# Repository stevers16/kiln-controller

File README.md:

# Kiln Controller

A MicroPython-based lumber drying kiln controller for a passive solar kiln in the
Georgian Bay area of Ontario. Designed for drying hardwood lumber (maple and beech,
0.5--1 inch thick) using multi-stage schedules derived from USDA Forest Products
Laboratory references (FPL-GTR-57 and FPL-GTR-118).

The kiln is approximately 5 ft x 2 ft x 3 ft, heated passively by solar gain with a
500W ceramic PTC backup heater for shoulder-season use. A Raspberry Pi Pico 2W
controls all kiln hardware. Telemetry is transmitted over LoRa (~200m) to a Raspberry
Pi 4 at the cottage, which stores data in SQLite and serves a REST API for a Kivy
mobile app.

---

## Hardware

| Subsystem | Component |
|---|---|
| MCU | Raspberry Pi Pico 2W |
| Temperature / RH | 2x SHT31-D (I2C, 0x44 / 0x45) |
| Moisture probes | Resistive, voltage divider, AC excitation |
| Exhaust fan | Foxconn PVA080G12Q 80mm PWM, tach feedback |
| Circulation fans | 3x Thermalright TL-C12C 120mm PWM |
| Vent dampers | 2x MG90S servo (intake + exhaust) |
| Backup heater | 500W PTC + Fotek SSR-25DA + RY85 thermal fuse |
| Current monitoring | 2x INA219 (12V rail + 5V rail) |
| Display | JC035-HVGA-ST-02 3.5" UART serial, 320x480 |
| SD card | SPI micro SD (logging) |
| LoRa radio | AI-Thinker Ra-02 433 MHz (SX1278), TX-only |
| Remote server | Raspberry Pi 4 with Ra-02 receiver |

---

## Schematic and custom PCB

KiCad 9.0 project with schematic and custom PCB layout is in the PCB folder.

---

## Firmware (Pico 2W -- MicroPython)

All hardware drivers live in `lib/`. Every module is class-based, accepts pin numbers
as constructor arguments, and follows the pattern established in `lib/exhaust.py`.

| Module | Function |
|---|---|
| `lib/exhaust.py` | 80mm exhaust fan -- PWM + tach |
| `lib/circulation.py` | 3x 120mm circulation fans -- PWM group |
| `lib/vents.py` | Intake + exhaust damper servos |
| `lib/heater.py` | SSR on/off control |
| `lib/SHT31sensors.py` | Dual SHT31 temperature + RH |
| `lib/moisture.py` | Resistive moisture probes, species correction |
| `lib/current.py` | INA219 DC current monitoring |
| `lib/lora.py` | SX1278 LoRa transmitter (TX-only, register polling) |
| `lib/display.py` | UART serial display driver + button + page system |
| `lib/sdcard.py` | SPI SD card mount/unmount wrapper |
| `lib/logger.py` | Event log + CSV data log to SD card |
| `lib/schedule.py` | Multi-stage drying schedule controller |
| `main.py` | Entry point -- asyncio control loop + WiFi AP + REST API |
| `config.py` | Deployment configuration (SSID, key, LoRa params) |

Drying schedules are stored as JSON in `schedules/` and loaded from the SD card at
runtime. Schedules are included for hard maple and beech at 0.5 in and 1 in thickness.

### Deploying to the Pico

```
python update_lib.py
```

This copies `main.py`, `config.py`, and all `lib/` files to the Pico in one step.
The MicroPython SPI SD card driver must be deployed as `sdcard_driver.py`:

```
mpremote cp sdcard_driver.py :sdcard_driver.py
```

### Running tests

```
mpremote run test_modules.py
```

Tests all 12 modules in sequence and reports pass/fail. Does not start WiFi or the
control loop.

---

## Cottage-side architecture (Pi4)

```
Pico --> SPI1 --> Ra-02 ~~LoRa~~ Ra-02 --> SPI0 --> Pi4 kiln_server
                                                 --> SQLite
                                                 --> REST API :8080 --> Kivy app
                                                 --> ntfy.sh --> phone
```

The `kiln_server/` Python package (in progress) runs as a systemd service on the Pi4.
It receives LoRa packets from the Pico, writes telemetry and alerts to SQLite, serves
a REST API for the mobile app, and pushes fault alerts via ntfy.sh.

The Pico also runs a WiFi AP and exposes its own REST API (port 80) for direct
local control when within range.

---

## Drying schedules

Schedules follow USDA FPL kiln-drying recommendations:

- Hard maple (T3-C2): `schedules/maple_05in.json`, `schedules/maple_1in.json`
- Beech (T4-C3): `schedules/beech_05in.json`, `schedules/beech_1in.json`

Each schedule has 9 stages: 7 drying stages + equalizing + conditioning. Stage advance
is automatic (MC% + minimum time) for drying stages, and time-only for
equalizing/conditioning. Manual advance is available via the REST API.

---

## Status

Pico firmware is at the integration stage. All 12 `lib/` modules are complete and
hardware-tested. `main.py` is implemented and pending full hardware integration test.
The Pi4 `kiln_server` daemon and Kivy mobile app are next.

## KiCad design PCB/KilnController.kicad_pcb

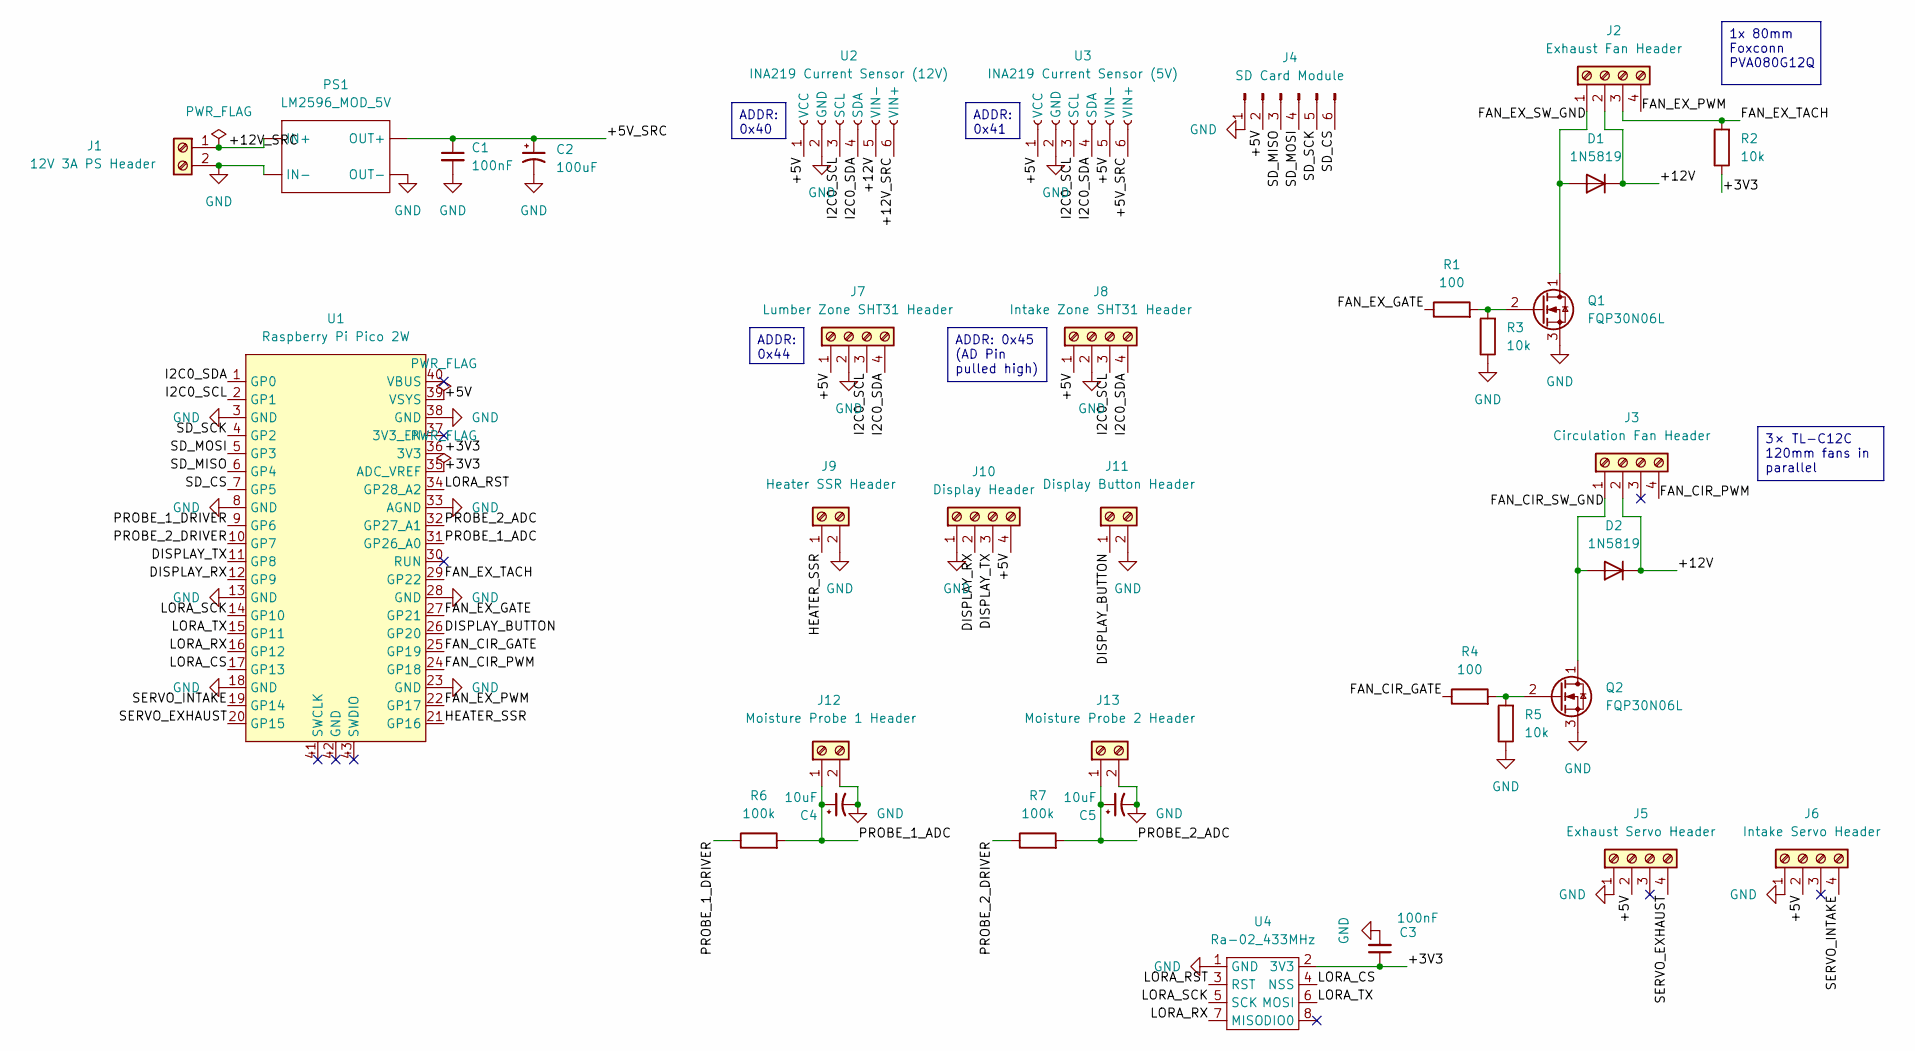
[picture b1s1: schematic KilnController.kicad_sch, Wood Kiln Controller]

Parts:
C1, C3: 100nF; C_Disc_D5.0mm_W2.5mm_P5.00mm
C2: 100uF; CP_Radial_D8.0mm_P3.50mm
C4, C5: 10uF; CP_Radial_D5.0mm_P2.00mm
D1, D2: 1N5819; D_DO-41_SOD81_P10.16mm_Horizontal
J1: 12V 3A PS Header; TerminalBlock_MetzConnect_Type101_RT01602HBWC_1x02_P5.08mm_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
J2: Exhaust Fan Header; TerminalBlock_MetzConnect_Type101_RT01604HBWC_1x04_P5.08mm_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
J3: Circulation Fan Header; TerminalBlock_MetzConnect_Type101_RT01604HBWC_1x04_P5.08mm_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
J4: SD Card Module; PinSocket_1x06_P2.54mm_Vertical
J5: Exhaust Servo Header; TerminalBlock_MetzConnect_Type101_RT01604HBWC_1x04_P5.08mm_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
J6: Intake Servo Header; TerminalBlock_MetzConnect_Type101_RT01604HBWC_1x04_P5.08mm_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
J7: Lumber Zone SHT31 Header; TerminalBlock_MetzConnect_Type101_RT01604HBWC_1x04_P5.08mm_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
J8: Intake Zone SHT31 Header; TerminalBlock_MetzConnect_Type101_RT01604HBWC_1x04_P5.08mm_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
J9: Heater SSR Header; TerminalBlock_MetzConnect_Type101_RT01602HBWC_1x02_P5.08mm_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
J10: Display Header; TerminalBlock_MetzConnect_Type101_RT01604HBWC_1x04_P5.08mm_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
J11: Display Button Header; TerminalBlock_MetzConnect_Type101_RT01602HBWC_1x02_P5.08mm_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
J12: Moisture Probe 1 Header; TerminalBlock_MetzConnect_Type101_RT01602HBWC_1x02_P5.08mm_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
J13: Moisture Probe 2 Header; TerminalBlock_MetzConnect_Type101_RT01602HBWC_1x02_P5.08mm_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
PS1: LM2596_MOD_5V; LM2596_Module_5V
Q1, Q2: FQP30N06L; TO-220-3_Vertical
R1, R4: 100; R_Axial_DIN0207_L6.3mm_D2.5mm_P10.16mm_Horizontal
R2, R3, R5: 10k; R_Axial_DIN0207_L6.3mm_D2.5mm_P10.16mm_Horizontal
R6, R7: 100k; R_Axial_DIN0207_L6.3mm_D2.5mm_P10.16mm_Horizontal
U1: Raspberry Pi Pico 2W; RaspberryPi_Pico_Common_THT
U2: INA219 Current Sensor (12V); INA219_Module
U3: INA219 Current Sensor (5V); INA219_Module
U4: Ra-02_433MHz; LoRa_Module

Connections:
/+3V3: C3.1, R2.1, U1.35 (ADC_VREF), U1.36 (3V3), U4.2 (3V3)
/+5V: J4.2, J5.2, J6.2, J7.1, J8.1, J10.4, U1.39 (VSYS), U2.1 (VCC), U3.1 (VCC), U3.5 (VIN-)
/+5V_SRC: C1.1, C2.1, PS1.3 (OUT+), U3.6 (VIN+)
/+12V: D1.1 (K), D2.1 (K), J2.2, J3.2, U2.5 (VIN-)
/+12V_SRC: J1.1, PS1.1 (IN+), U2.6 (VIN+)
/DISPLAY_BUTTON: J11.1, U1.26 (GP20)
/DISPLAY_RX: J10.2, U1.12 (GP9)
/DISPLAY_TX: J10.3, U1.11 (GP8)
/FAN_CIR_GATE: R4.1, U1.25 (GP19)
/FAN_CIR_PWM: J3.4, U1.24 (GP18)
/FAN_CIR_SW_GND: D2.2 (A), J3.1, Q2.1 (D)
/FAN_EX_GATE: R1.1, U1.27 (GP21)
/FAN_EX_PWM: J2.4, U1.22 (GP17)
/FAN_EX_SW_GND: D1.2 (A), J2.1, Q1.1 (D)
/FAN_EX_TACH: J2.3, R2.2, U1.29 (GP22)
/HEATER_SSR: J9.1, U1.21 (GP16)
/I2C0_SCL: J7.3, J8.3, U1.2 (GP1), U2.3 (SCL), U3.3 (SCL)
/I2C0_SDA: J7.4, J8.4, U1.1 (GP0), U2.4 (SDA), U3.4 (SDA)
/LORA_CS: U1.17 (GP13), U4.4 (NSS)
/LORA_RST: U1.34 (GP28_A2), U4.3 (RST)
/LORA_RX: U1.16 (GP12), U4.7 (MISO)
/LORA_SCK: U1.14 (GP10), U4.5 (SCK)
/LORA_TX: U1.15 (GP11), U4.6 (MOSI)
/PROBE_1_ADC: C4.1, J12.1, R6.2, U1.31 (GP26_A0)
/PROBE_1_DRIVER: R6.1, U1.9 (GP6)
/PROBE_2_ADC: C5.1, J13.1, R7.2, U1.32 (GP27_A1)
/PROBE_2_DRIVER: R7.1, U1.10 (GP7)
/SD_CS: J4.6, U1.7 (GP5)
/SD_MISO: J4.3, U1.6 (GP4)
/SD_MOSI: J4.4, U1.5 (GP3)
/SD_SCK: J4.5, U1.4 (GP2)
/SERVO_EXHAUST: J5.4, U1.20 (GP15)
/SERVO_INTAKE: J6.4, U1.19 (GP14)
GND: C1.2, C2.2, C3.2, C4.2, C5.2, J1.2, J4.1, J5.1, J6.1, J7.2, J8.2, J9.2, J10.1, J11.2, J12.2, J13.2, PS1.2 (IN-), PS1.4 (OUT-), Q1.3 (S), Q2.3 (S), R3.1, R5.1, U1.3 (GND), U1.8 (GND), U1.13 (GND), U1.18 (GND), U1.23 (GND), U1.28 (GND), U1.33 (AGND), U1.38 (GND), U2.2 (GND), U3.2 (GND), U4.1 (GND)
unnamed: Q1.2 (G), R1.2, R3.2
unnamed: Q2.2 (G), R4.2, R5.2

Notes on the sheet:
1x 80mm Foxconn PVA080G12Q
ADDR: 0x45 (AD Pin pulled high)
ADDR: 0x40
3× TL-C12C 120mm fans in parallel
ADDR: 0x41
ADDR: 0x44

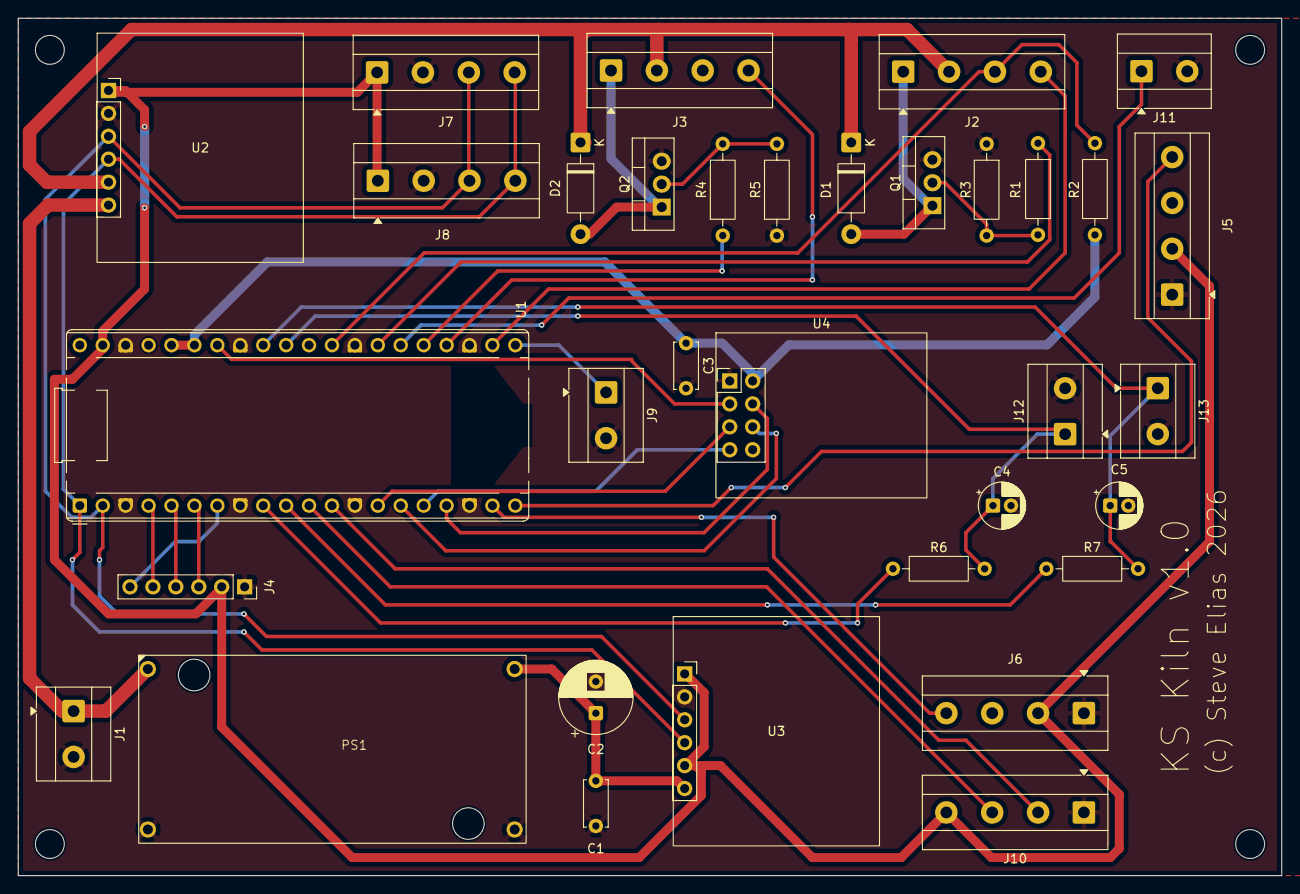
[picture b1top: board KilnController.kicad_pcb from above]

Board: 2 copper layers, 140.0 x 95.0 mm, 34 parts (0 on the bottom side), 36 nets.

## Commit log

2026-03-18 Initial commit including logging library
2026-03-18 Resolved SDCard issues
2026-03-18 Add vent servo module
2026-03-21 Add KiCad project
2026-03-21 Current monitoring WIP
2026-03-22 Working current monitors, with updated layout
2026-03-22 Controller and KiCad for SHT31D sensors
2026-03-22 Heater SSR controller and PCB update
2026-03-25 Working display driver with schematic and layout
2026-03-25 Update Display Button GPIO
2026-03-28 Add moisture.py
2026-03-28 Add schedule controller plus misc. fixes
2026-03-28 Additional specs and small updates
2026-03-28 Add main.py with REST API
2026-04-03 Minor updates and lora spec reconcile
2026-04-03 Working LORA communication
2026-04-03 Add LoRa to schematic & layout
2026-04-06 Updates for boot safety and AP connection
2026-04-08 Remove VBUS connection
2026-04-08 Drawing
2026-04-08 Cleanup & readme
2026-04-08 Remove spec documents section from README
    Removed specification documents section from README.
2026-04-08 Add schematic and PCB information to README
    Added section for schematic and custom PCB details.
2026-04-08 Initial commit of the Kivy app
2026-04-09 Kivy Settings and Dashboard working
2026-04-09 Schedule run WIP
2026-04-09 Dynamic dashboard updates during drying
2026-04-09 Kivy WIP prior to addressing firmware issue
2026-04-10 PCB V1 before redesign
2026-04-12 PCB design V2
2026-04-12 Surface errors from the firmware to API.
2026-04-12 Minor firmware cleanup
2026-04-12 Minor GP reordering
2026-04-13 V3 PBC Design
2026-04-19 Final PCB for manufacturing
2026-04-19 Add Runs screen to Kivy app
2026-04-19 Pi4 demon initial version
2026-04-19 Run history graphs
2026-04-21 Add run start menu
2026-04-21 Firmware fixes
2026-04-21 LoRa Fault notifier
2026-04-21 Schedule creation and editing
2026-04-22 Add full System Test
2026-04-22 Logs screen
2026-04-22 Moisture probe calibration screen
2026-04-22 Module upload
2026-04-29 Cottage server updates
2026-04-29 kiln_server cleanup
2026-04-29 App cleanup
2026-04-30 Initial updates for phone builds.
2026-05-01 Android app polish
